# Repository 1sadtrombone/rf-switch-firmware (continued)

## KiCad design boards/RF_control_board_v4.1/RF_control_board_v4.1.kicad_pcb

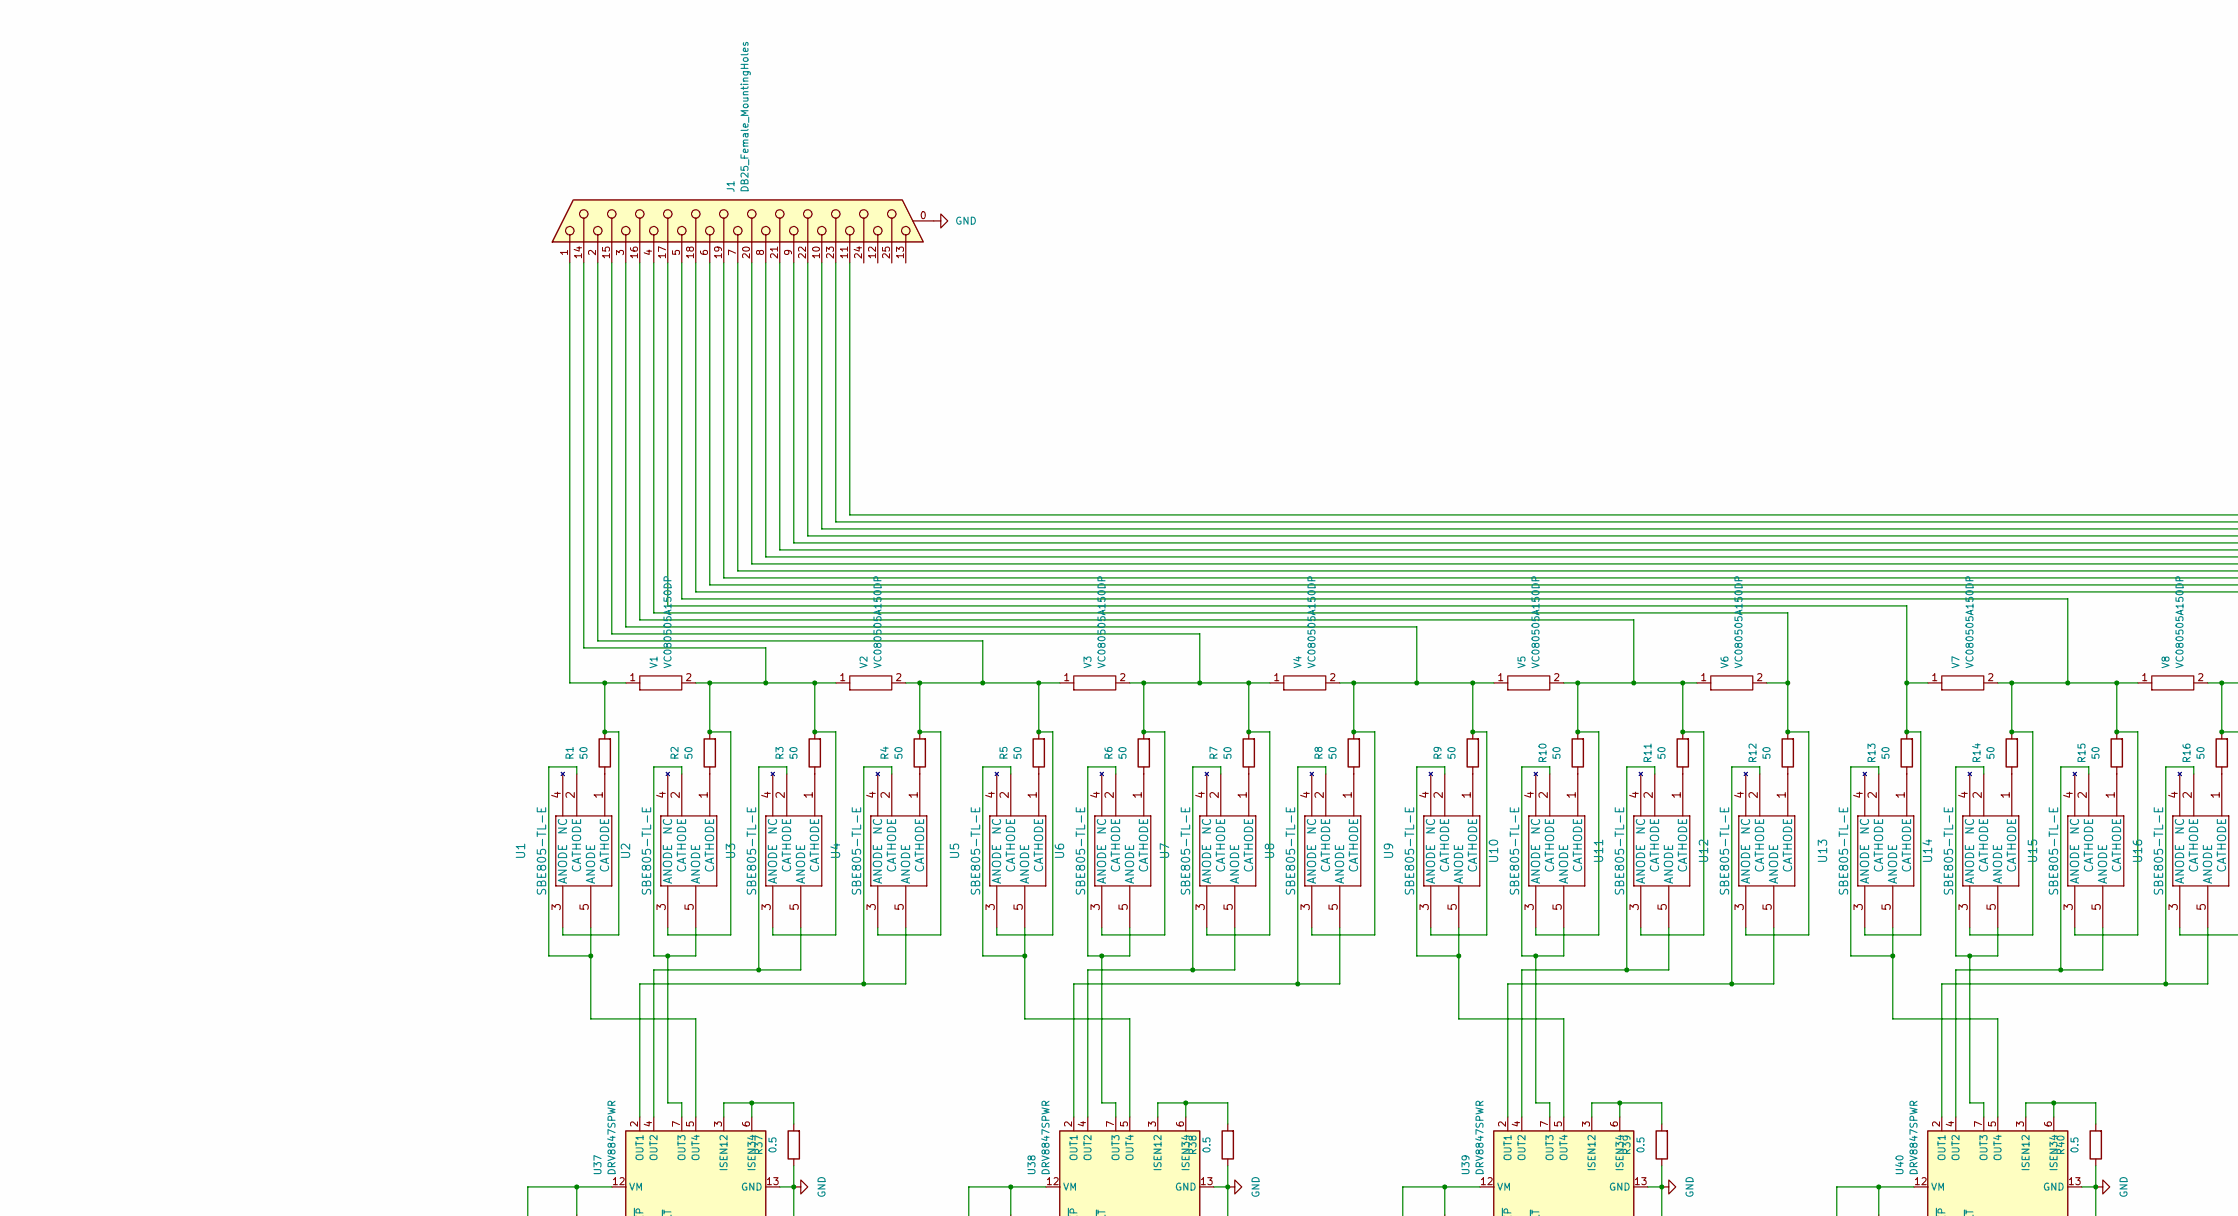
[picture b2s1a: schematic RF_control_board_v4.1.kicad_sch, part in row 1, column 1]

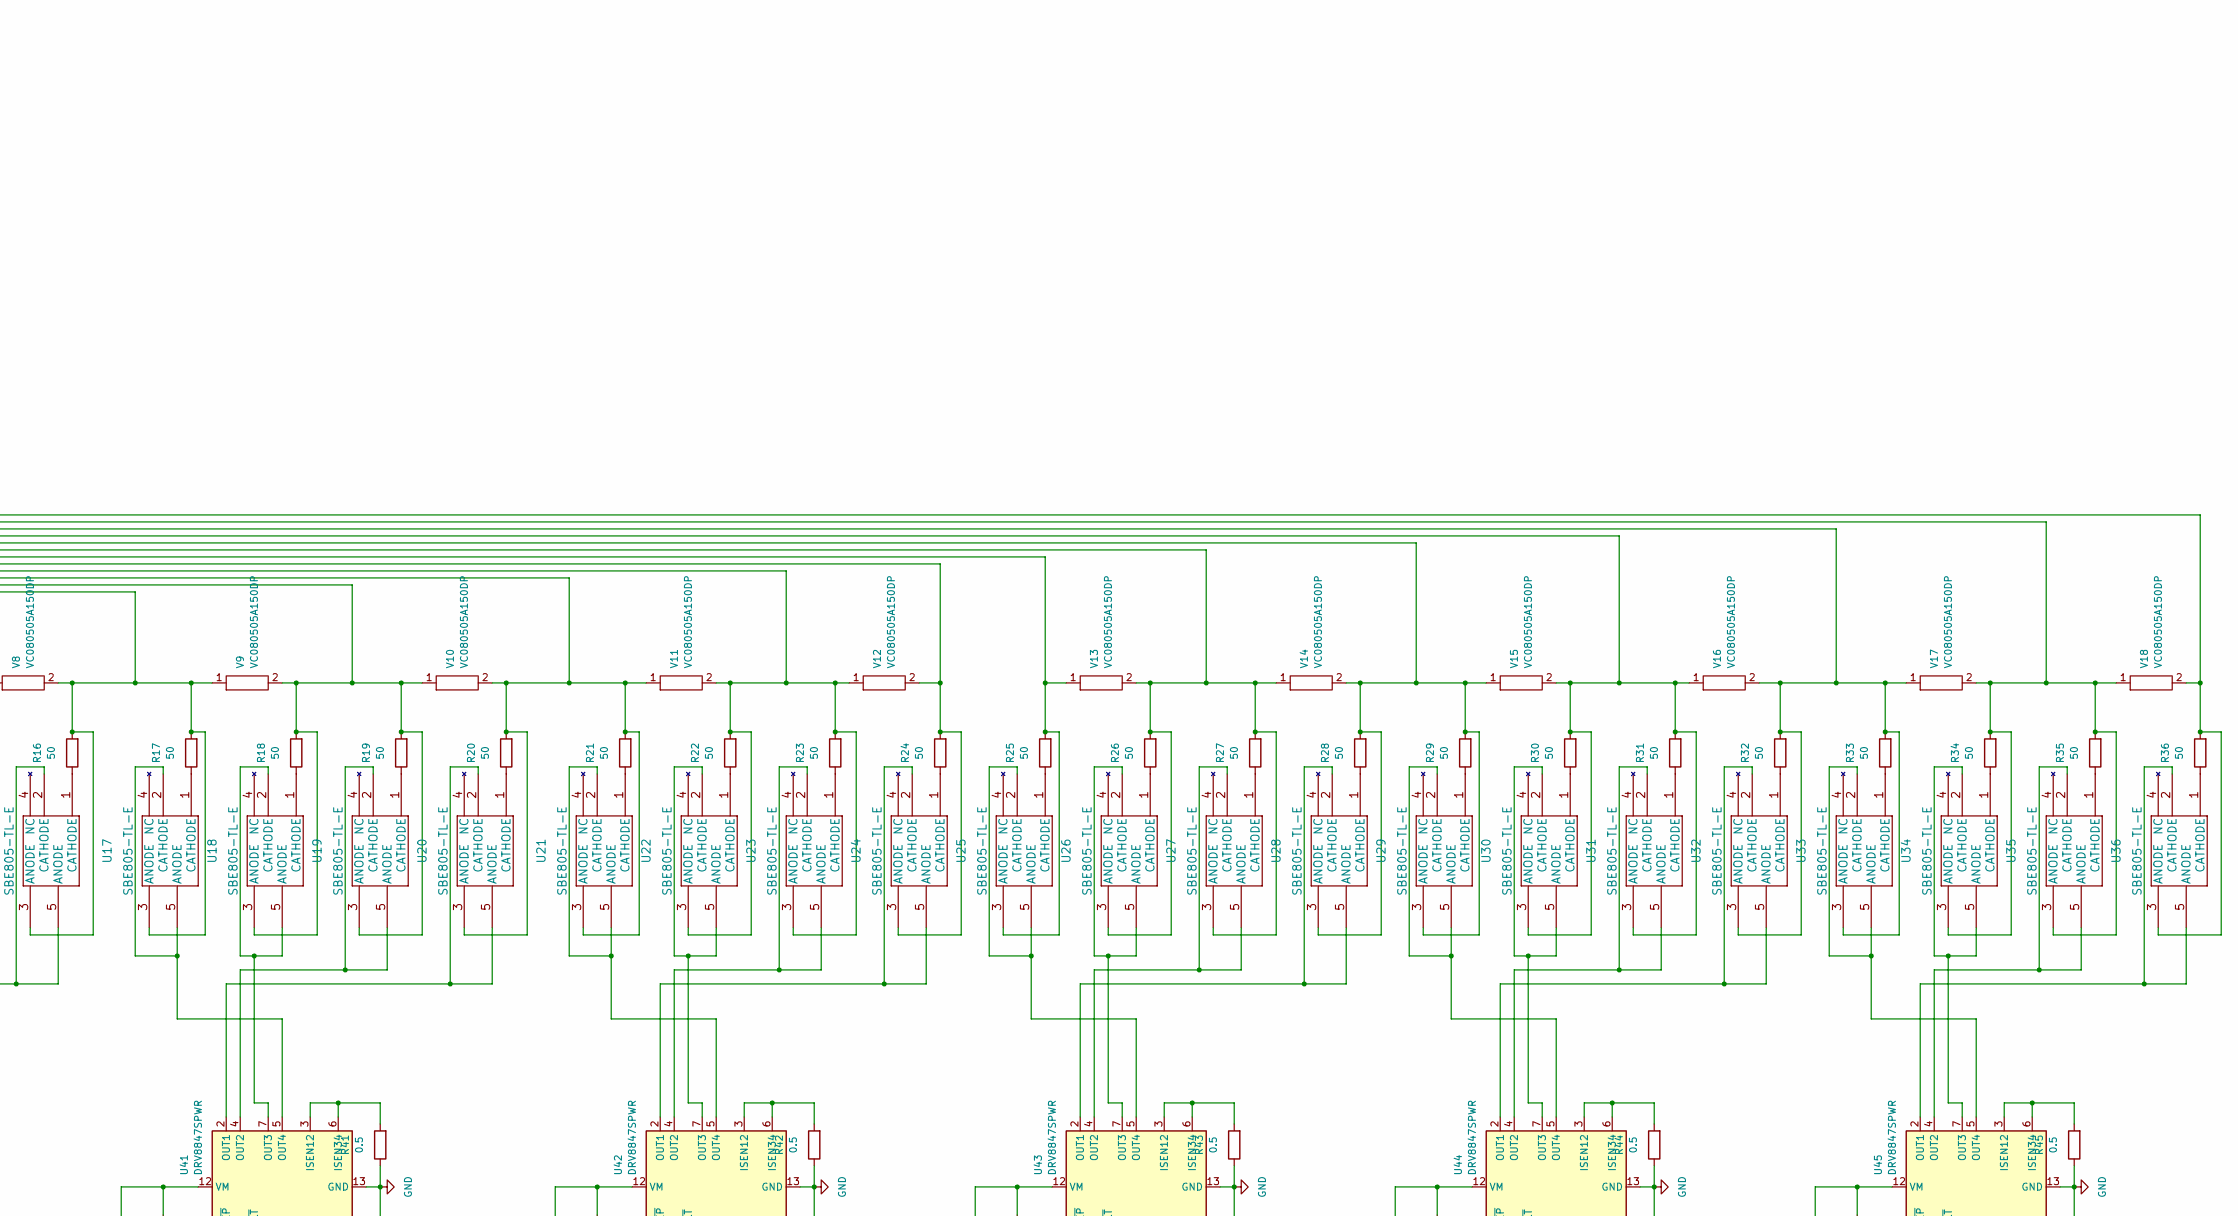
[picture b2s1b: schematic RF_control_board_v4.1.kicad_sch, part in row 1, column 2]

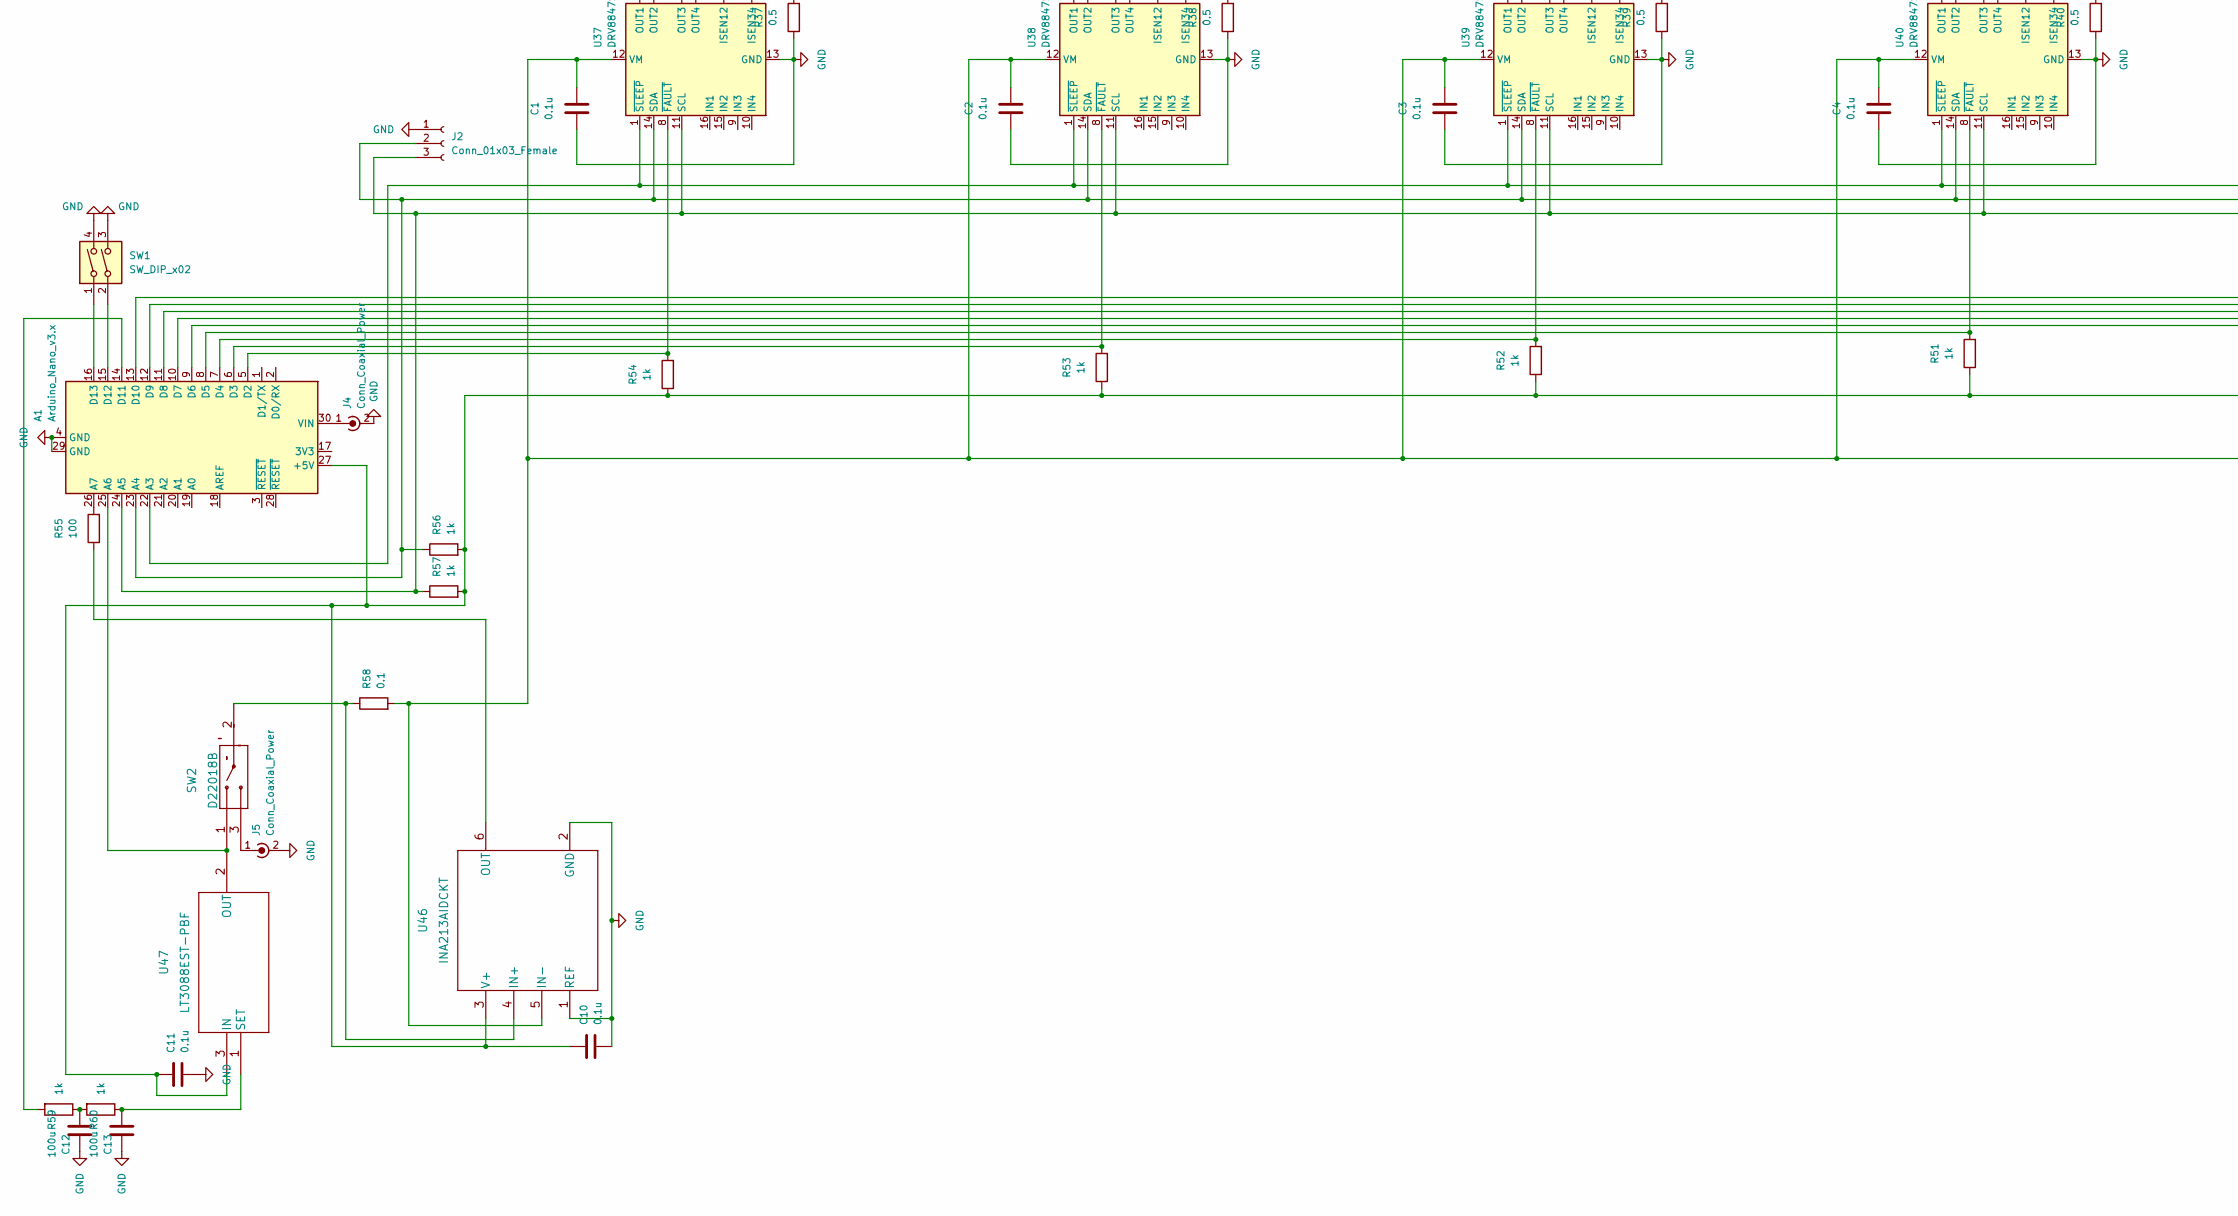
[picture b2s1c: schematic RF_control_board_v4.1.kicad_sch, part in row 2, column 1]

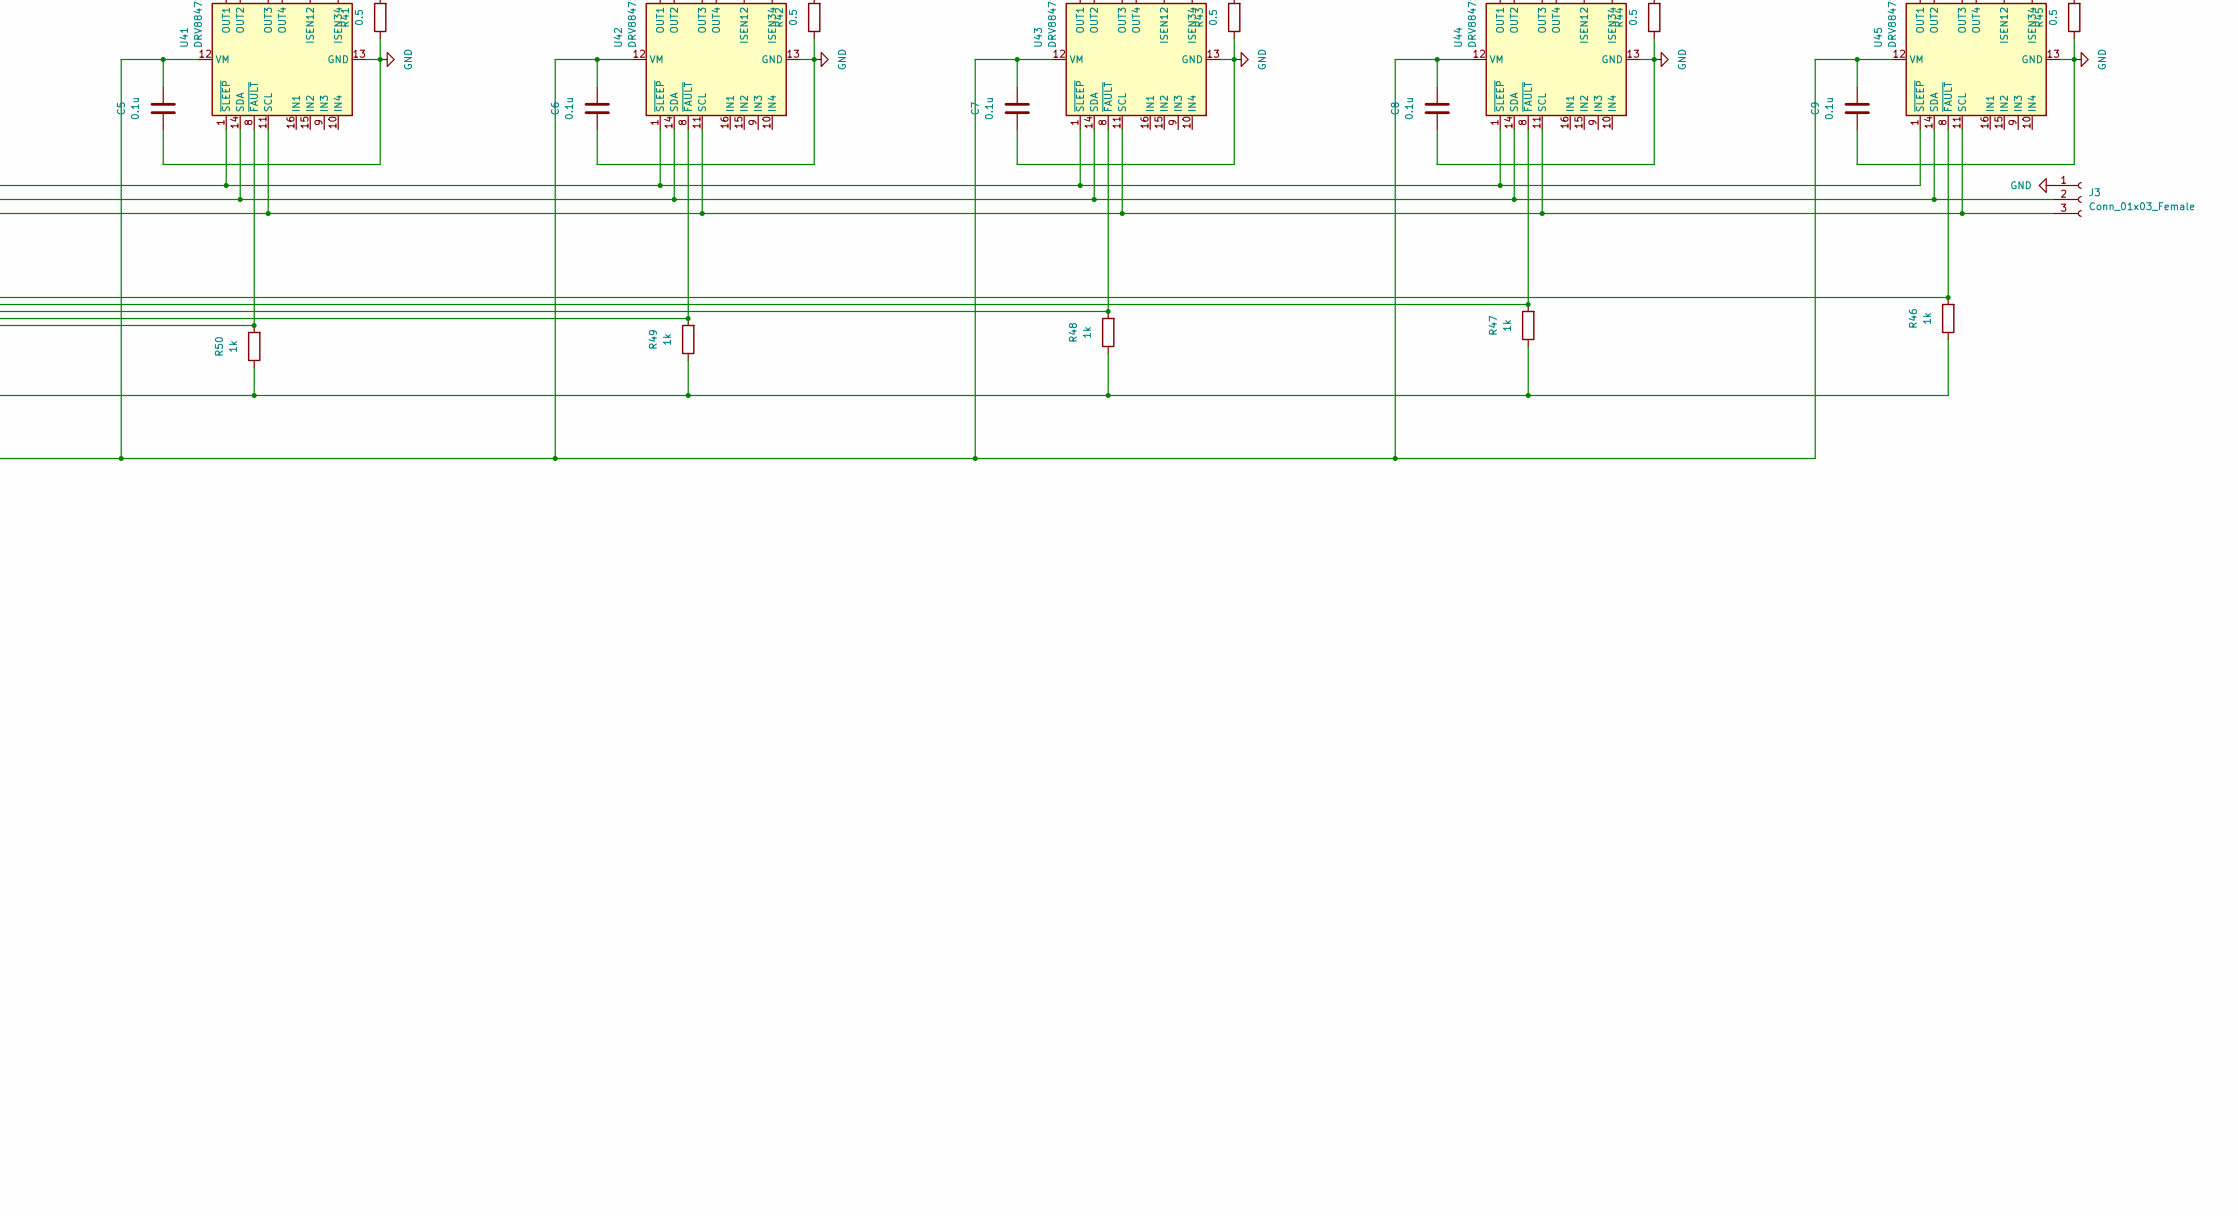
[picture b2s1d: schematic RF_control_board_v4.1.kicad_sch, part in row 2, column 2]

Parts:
A1: Arduino_Nano_v3.x; Arduino_Nano
C1, C2, C3, C4, C5, C6, C7, C8, C9, C10, C11: 0.1u; C_0603_1608Metric
C12, C13: 100u; C_0805_2012Metric
J1: DB25_Female_MountingHoles; DSUB-25_Female_Horizontal_P2.77x2.84mm_EdgePinOffset4.94mm_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
J2, J3: Conn_01x03_Female; JST_GH_BM03B-GHS-TBT_1x03-1MP_P1.25mm_Vertical
J4: Conn_Coaxial_Power; BarrelJack_CUI_PJ-063AH_Horizontal
J5: Conn_Coaxial_Power; BNC_Amphenol_B6252HB-NPP3G-50_Horizontal
R1, R2, R3, R4, R5, R6, R7, R8, R9, R10, R11, R12, R13, R14, R15, R16, R17, R18, R19, R20, R21, R22, R23, R24, R25, R26, R27, R28, R29, R30, R31, R32, R33, R34, R35, R36: 50; R_0603_1608Metric
R37, R38, R39, R40, R41, R42, R43, R44, R45: 0.5; R_0603_1608Metric
R46, R47, R48, R49, R50, R51, R52, R53, R54, R56, R57, R59, R60: 1k; R_0603_1608Metric
R55: 100; R_0603_1608Metric
R58: 0.1; R_0603_1608Metric
SW1: SW_DIP_x02; SW_DIP_SPSTx02_Slide_9.78x7.26mm_W7.62mm_P2.54mm
SW2: D22018B; D22012_B_NKK
U1, U2, U3, U4, U5, U6, U7, U8, U9, U10, U11, U12, U13, U14, U15, U16, U17, U18, U19, U20, U21, U22, U23, U24, U25, U26, U27, U28, U29, U30, U31, U32, U33, U34, U35, U36: SBE805-TL-E; SOT-753_1P6X2P9_ONS
U37, U38, U39, U40, U41, U42, U43, U44, U45: DRV8847SPWR; TSSOP-16_4.4x5mm_P0.65mm
U46: INA213AIDCKT; DCK0006A_N
U47: LT3088EST-PBF; SOT-223_ST_LIT
V1, V2, V3, V4, V5, V6, V7, V8, V9, V10, V11, V12, V13, V14, V15, V16, V17, V18: VC080505A150DP; R_0805_2012Metric

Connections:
GND: A1.4 (GND), A1.29 (GND), C1.1, C2.1, C3.1, C4.1, C5.1, C6.1, C7.1, C8.1, C9.1, C10.1, C11.2, C12.2, C13.2, J1.0 (PAD), J2.1, J3.1, J4.2 (Ext), J5.2 (Ext), R37.1, R38.1, R39.1, R40.1, R41.1, R42.1, R43.1, R44.1, R45.1, SW1.3, SW1.4, U37.13 (GND), U38.13 (GND), U39.13 (GND), U40.13 (GND), U41.13 (GND), U42.13 (GND), U43.13 (GND), U44.13 (GND), U45.13 (GND), U46.1 (REF), U46.2 (GND)
unnamed: A1.5 (D2), R54.2, U37.8 (~FAULT)
unnamed: A1.6 (D3), R53.2, U38.8 (~FAULT)
unnamed: A1.7 (D4), R52.2, U39.8 (~FAULT)
unnamed: A1.8 (D5), R51.2, U40.8 (~FAULT)
unnamed: A1.9 (D6), R50.2, U41.8 (~FAULT)
unnamed: A1.10 (D7), R49.2, U42.8 (~FAULT)
unnamed: A1.11 (D8), R48.2, U43.8 (~FAULT)
unnamed: A1.12 (D9), R47.2, U44.8 (~FAULT)
unnamed: A1.13 (D10), R46.2, U45.8 (~FAULT)
unnamed: A1.14 (D11), R59.2
unnamed: A1.15 (D12), SW1.2
unnamed: A1.16 (D13), SW1.1
unnamed: A1.22 (A3), U37.1 (~SLEEP), U38.1 (~SLEEP), U39.1 (~SLEEP), U40.1 (~SLEEP), U41.1 (~SLEEP), U42.1 (~SLEEP), U43.1 (~SLEEP), U44.1 (~SLEEP), U45.1 (~SLEEP)
unnamed: A1.23 (A4), J2.2, J3.2, R56.1, U37.14 (SDA), U38.14 (SDA), U39.14 (SDA), U40.14 (SDA), U41.14 (SDA), U42.14 (SDA), U43.14 (SDA), U44.14 (SDA), U45.14 (SDA)
unnamed: A1.24 (A5), J2.3, J3.3, R57.1, U37.11 (SCL), U38.11 (SCL), U39.11 (SCL), U40.11 (SCL), U41.11 (SCL), U42.11 (SCL), U43.11 (SCL), U44.11 (SCL), U45.11 (SCL)
unnamed: A1.25 (A6), SW2.1, U47.2 (OUT)
unnamed: A1.26 (A7), R55.2
unnamed: A1.27 (+5V), C10.2, C11.1, R46.1, R47.1, R48.1, R49.1, R50.1, R51.1, R52.1, R53.1, R54.1, R56.2, R57.2, U46.3 (V+), U47.3 (IN)
unnamed: A1.30 (VIN), J4.1 (In)
unnamed: C1.2, C2.2, C3.2, C4.2, C5.2, C6.2, C7.2, C8.2, C9.2, R58.2, U37.12 (VM), U38.12 (VM), U39.12 (VM), U40.12 (VM), U41.12 (VM), U42.12 (VM), U43.12 (VM), U44.12 (VM), U45.12 (VM), U46.5 (IN-)
unnamed: C12.1, R59.1, R60.2
unnamed: C13.1, R60.1, U47.1 (SET)
unnamed: J1.1, R1.2, U1.3 (ANODE), V1.1
unnamed: J1.2, R4.2, R5.2, U4.3 (ANODE), U5.3 (ANODE), V2.2, V3.1
unnamed: J1.3, R8.2, R9.2, U8.3 (ANODE), U9.3 (ANODE), V4.2, V5.1
unnamed: J1.4, R12.2, U12.3 (ANODE), V6.2
unnamed: J1.5, R14.2, R15.2, U14.3 (ANODE), U15.3 (ANODE), V7.2, V8.1
unnamed: J1.6, R18.2, R19.2, U18.3 (ANODE), U19.3 (ANODE), V9.2, V10.1
unnamed: J1.7, R22.2, R23.2, U22.3 (ANODE), U23.3 (ANODE), V11.2, V12.1
unnamed: J1.8, R25.2, U25.3 (ANODE), V13.1
unnamed: J1.9, R28.2, R29.2, U28.3 (ANODE), U29.3 (ANODE), V14.2, V15.1
unnamed: J1.10, R32.2, R33.2, U32.3 (ANODE), U33.3 (ANODE), V16.2, V17.1
unnamed: J1.11, R36.2, U36.3 (ANODE), V18.2
unnamed: J1.14, R2.2, R3.2, U2.3 (ANODE), U3.3 (ANODE), V1.2, V2.1
unnamed: J1.15, R6.2, R7.2, U6.3 (ANODE), U7.3 (ANODE), V3.2, V4.1
unnamed: J1.16, R10.2, R11.2, U10.3 (ANODE), U11.3 (ANODE), V5.2, V6.1
unnamed: J1.17, R13.2, U13.3 (ANODE), V7.1
unnamed: J1.18, R16.2, R17.2, U16.3 (ANODE), U17.3 (ANODE), V8.2, V9.1
unnamed: J1.19, R20.2, R21.2, U20.3 (ANODE), U21.3 (ANODE), V10.2, V11.1
unnamed: J1.20, R24.2, U24.3 (ANODE), V12.2
unnamed: J1.21, R26.2, R27.2, U26.3 (ANODE), U27.3 (ANODE), V13.2, V14.1
unnamed: J1.22, R30.2, R31.2, U30.3 (ANODE), U31.3 (ANODE), V15.2, V16.1
unnamed: J1.23, R34.2, R35.2, U34.3 (ANODE), U35.3 (ANODE), V17.2, V18.1
unnamed: J5.1 (In), SW2.3
unnamed: R1.1, U1.1 (CATHODE)
unnamed: R2.1, U2.1 (CATHODE)
unnamed: R3.1, U3.1 (CATHODE)
unnamed: R4.1, U4.1 (CATHODE)
unnamed: R5.1, U5.1 (CATHODE)
unnamed: R6.1, U6.1 (CATHODE)
unnamed: R7.1, U7.1 (CATHODE)
unnamed: R8.1, U8.1 (CATHODE)
unnamed: R9.1, U9.1 (CATHODE)
unnamed: R10.1, U10.1 (CATHODE)
unnamed: R11.1, U11.1 (CATHODE)
unnamed: R12.1, U12.1 (CATHODE)
unnamed: R13.1, U13.1 (CATHODE)
unnamed: R14.1, U14.1 (CATHODE)
unnamed: R15.1, U15.1 (CATHODE)
unnamed: R16.1, U16.1 (CATHODE)
unnamed: R17.1, U17.1 (CATHODE)
unnamed: R18.1, U18.1 (CATHODE)
unnamed: R19.1, U19.1 (CATHODE)
unnamed: R20.1, U20.1 (CATHODE)
unnamed: R21.1, U21.1 (CATHODE)
unnamed: R22.1, U22.1 (CATHODE)
unnamed: R23.1, U23.1 (CATHODE)
unnamed: R24.1, U24.1 (CATHODE)
unnamed: R25.1, U25.1 (CATHODE)
unnamed: R26.1, U26.1 (CATHODE)
unnamed: R27.1, U27.1 (CATHODE)
unnamed: R28.1, U28.1 (CATHODE)
unnamed: R29.1, U29.1 (CATHODE)
unnamed: R30.1, U30.1 (CATHODE)
unnamed: R31.1, U31.1 (CATHODE)
unnamed: R32.1, U32.1 (CATHODE)
unnamed: R33.1, U33.1 (CATHODE)
unnamed: R34.1, U34.1 (CATHODE)
unnamed: R35.1, U35.1 (CATHODE)
unnamed: R36.1, U36.1 (CATHODE)
unnamed: R37.2, U37.3 (ISEN12), U37.6 (ISEN34)
unnamed: R38.2, U38.3 (ISEN12), U38.6 (ISEN34)
unnamed: R39.2, U39.3 (ISEN12), U39.6 (ISEN34)
unnamed: R40.2, U40.3 (ISEN12), U40.6 (ISEN34)
unnamed: R41.2, U41.3 (ISEN12), U41.6 (ISEN34)
unnamed: R42.2, U42.3 (ISEN12), U42.6 (ISEN34)
unnamed: R43.2, U43.3 (ISEN12), U43.6 (ISEN34)
unnamed: R44.2, U44.3 (ISEN12), U44.6 (ISEN34)
unnamed: R45.2, U45.3 (ISEN12), U45.6 (ISEN34)
unnamed: R55.1, U46.6 (OUT)
unnamed: R58.1, SW2.2, U46.4 (IN+)
unnamed: U1.2 (CATHODE), U1.5 (ANODE), U37.5 (OUT4)
unnamed: U2.2 (CATHODE), U2.5 (ANODE), U37.7 (OUT3)
unnamed: U3.2 (CATHODE), U3.5 (ANODE), U37.4 (OUT2)
unnamed: U10.2 (CATHODE), U10.5 (ANODE), U39.7 (OUT3)
unnamed: U11.2 (CATHODE), U11.5 (ANODE), U39.4 (OUT2)
unnamed: U12.2 (CATHODE), U12.5 (ANODE), U39.2 (OUT1)
unnamed: U13.2 (CATHODE), U13.5 (ANODE), U40.5 (OUT4)
unnamed: U14.2 (CATHODE), U14.5 (ANODE), U40.7 (OUT3)
unnamed: U15.2 (CATHODE), U15.5 (ANODE), U40.4 (OUT2)
unnamed: U16.2 (CATHODE), U16.5 (ANODE), U40.2 (OUT1)
unnamed: U17.2 (CATHODE), U17.5 (ANODE), U41.5 (OUT4)
unnamed: U18.2 (CATHODE), U18.5 (ANODE), U41.7 (OUT3)
unnamed: U19.2 (CATHODE), U19.5 (ANODE), U41.4 (OUT2)
unnamed: U20.2 (CATHODE), U20.5 (ANODE), U41.2 (OUT1)
unnamed: U21.2 (CATHODE), U21.5 (ANODE), U42.5 (OUT4)
unnamed: U22.2 (CATHODE), U22.5 (ANODE), U42.7 (OUT3)
unnamed: U23.2 (CATHODE), U23.5 (ANODE), U42.4 (OUT2)
unnamed: U24.2 (CATHODE), U24.5 (ANODE), U42.2 (OUT1)
unnamed: U25.2 (CATHODE), U25.5 (ANODE), U43.5 (OUT4)
unnamed: U26.2 (CATHODE), U26.5 (ANODE), U43.7 (OUT3)
unnamed: U27.2 (CATHODE), U27.5 (ANODE), U43.4 (OUT2)
unnamed: U28.2 (CATHODE), U28.5 (ANODE), U43.2 (OUT1)
unnamed: U29.2 (CATHODE), U29.5 (ANODE), U44.5 (OUT4)
unnamed: U30.2 (CATHODE), U30.5 (ANODE), U44.7 (OUT3)
unnamed: U31.2 (CATHODE), U31.5 (ANODE), U44.4 (OUT2)
unnamed: U32.2 (CATHODE), U32.5 (ANODE), U44.2 (OUT1)
unnamed: U33.2 (CATHODE), U33.5 (ANODE), U45.5 (OUT4)
unnamed: U34.2 (CATHODE), U34.5 (ANODE), U45.7 (OUT3)
unnamed: U35.2 (CATHODE), U35.5 (ANODE), U45.4 (OUT2)
unnamed: U36.2 (CATHODE), U36.5 (ANODE), U45.2 (OUT1)
unnamed: U4.2 (CATHODE), U4.5 (ANODE), U37.2 (OUT1)
unnamed: U8.2 (CATHODE), U8.5 (ANODE), U38.2 (OUT1)
unnamed: U7.2 (CATHODE), U7.5 (ANODE), U38.4 (OUT2)
unnamed: U5.2 (CATHODE), U5.5 (ANODE), U38.5 (OUT4)
unnamed: U6.2 (CATHODE), U6.5 (ANODE), U38.7 (OUT3)
unnamed: U9.2 (CATHODE), U9.5 (ANODE), U39.5 (OUT4)

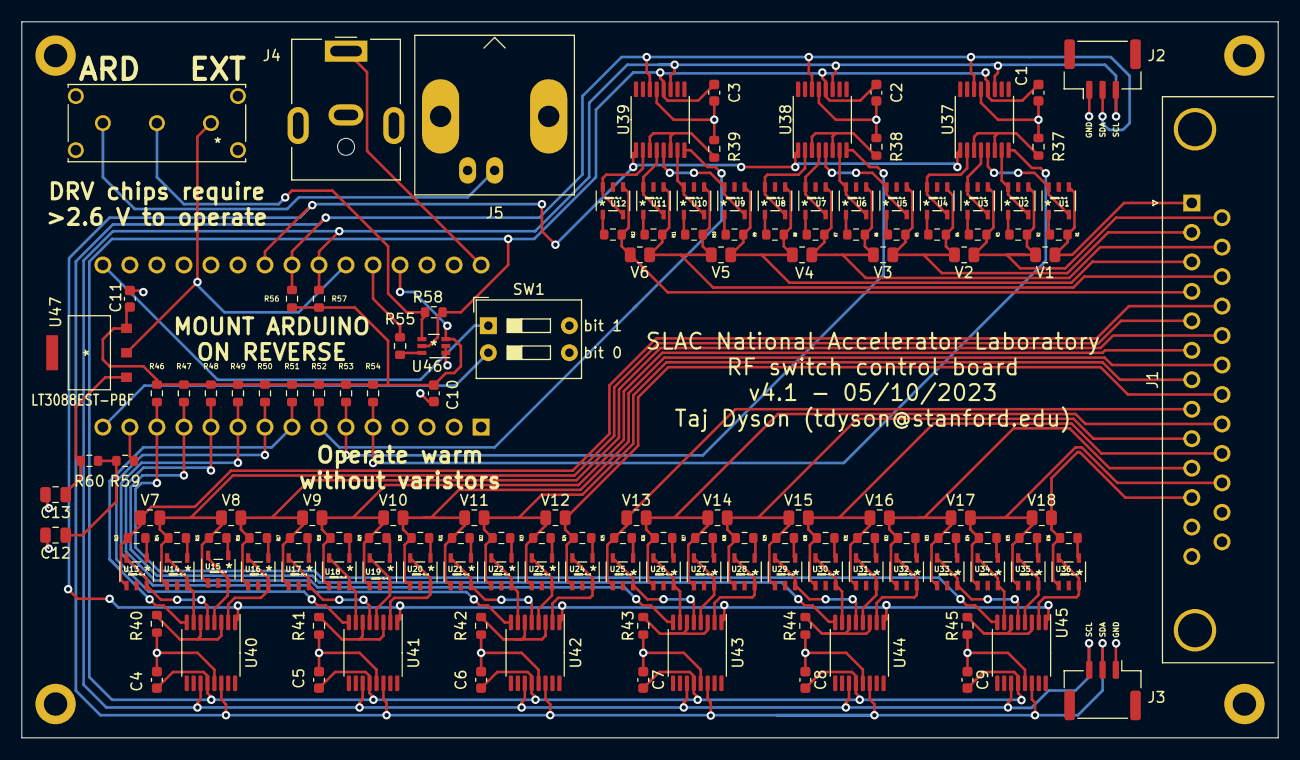
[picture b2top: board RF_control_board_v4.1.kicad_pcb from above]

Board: 2 copper layers, 118.1 x 67.3 mm, 146 parts (1 on the bottom side), 128 nets.

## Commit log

2023-06-08 Added firmware for controlling 4 independent 2-way failsafe switches
2023-06-08 Added KiCAD projects for v2 and v4.1 boards
2023-06-08 moved firmware to its own folder
2023-06-08 trimmed 2-way firmware
2023-06-08 added updated schematic for v4.1 board.
2023-06-08 removed unnecessary printing
2023-06-08 Added v4 firmware, starting from v1 and adding current sense
2023-06-08 implemented delay()-less pulsing and the v2 commands (except all, which would be complicated)
2023-06-08 added setting arduino power to init
2023-06-08 changed reported voltage unit
2023-08-03 fixed the opn/cls confusion, and a bug meaning switch 3 wouldn't init
2023-09-06 fixed the open/close swap confusion
2023-09-07 reversed the previous change, which was somehow wrong
2023-09-13 added script that switches 1, 1 every 10 seconds for heating tests
2023-09-13 fixed mistakes
2023-09-13 fixed typo
2023-09-13 solved overflow issue with unsigned var
